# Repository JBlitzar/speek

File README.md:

# speek

A modular speaker system. Right now, it has a couple of boards:

- Speek Amp: This is the flagship amplifier. It's a hybrid 2.1 design using the TPA3116D2 chip. It's built to handle 4Ω speakers. It outputs lines for a mono subwoofer, two stereo woofers, and two stereo tweeters.
- Speek RX: This is a Bluetooth audio receiver. It runs off of a qfn esp32 D0WD v3 and has a built-in headphone amp, or a normal line out for chaining.
- Speek PSU: This is a supporting PSU board. It has a USB-C PD trigger (for quick tests) and a barrel jack port for proper power (needed to power real flagship drivers). It can be used as a stable power source for pretty much anything. Note that the barrel jack supplies 24V while PD gives 20V. 

On modularity:

- Each board is self-contained and can be used on its own. However, they can also all be used together. 

I made this project to get into audio systems! I've visited some hi-fi listening rooms, and I thought it was really cool. But I think the speaker industry is way overpriced. People commonly pay several thousand dollars for nice speaker systems! I wanted to build one myself for a few hundred. It might not be as high-fidelity, but it'll be my own, which is pretty cool. And you or I probably wouldn't be able to hear the difference. 

**Right now, enclosure design is out of scope. This repo holds just the boards, and the boards are complete**

## \[Please Read\] Where do I find everything? AKA checklist

What's with the monorepo?

A monorepo just means everything lives in one repo instead of splitting each board into its own. All the files are here: each board gets its own top-level folder (`speek-amp`, `speek-rx`, `speek-psu`), with docs in `docs` and the overall BOM at `BOM.csv`. I went with a monorepo because even though there are multiple boards, it's really one project overall, so it made sense to keep them together.

Checklist:

- [x] A good README
- [x] Source files for your project
    - This includes hardware design, firmware, 3D assemblies, etc
- [x] Production files (if applicable)
    - You'll find gerbers, fabrication BOMs, and PnP files at the following locations:
      - Speek Amp: [speek-amp/PCB/speek_amp/production_real](speek-amp/PCB/speek_amp/production_real)
      - Speek RX: [speek-rx/PCB/speek_rx/production_real](speek-rx/PCB/speek_rx/production_real)
      - Speek PSU: [speek-psu/PCB/speek_psu/production_real](speek-psu/PCB/speek_psu/production_real)
- \[N/A\] JOURNAL.md if journalling on Git
- [x] BOM.csv complete with functioning links (where applicable)
- [x] A short description of what your project is
- [x] A couple sentences on why you made the project
- [x] PICTURES OF YOUR PROJECT
- [x] A screenshot of your PCB, if you have one
- [x] A screenshot of your schematic, if you have one
- [x] A wiring diagram, if you're doing any wiring that isn't on a PCB
- [x] A BOM in table format at the end of the README
- [x] A STEP file of your assembly: [speek_assembly.step](docs/speek_assembly.step)

## How to use?

Mostly it's plug-and-play after assembling everything. The exception is Speek RX, which requires firmware to be flashed. See [speek-rx/README.md](speek-rx/README.md) for more info, but in short, all you should need to do is

```bash
cd speek-rx
cd firmware
pio run -t upload
```

For wiring your speaker drivers, the silkscreen should coach you through that. 

## Wiring Diagram

## Gallery

### Speek Amp

### Speek RX

### Speek PSU

## Schematics

### Speek Amp

[View on KiCanvas](https://kicanvas.org/?repo=https%3A%2F%2Fgithub.com%2FJBlitzar%2Fspeek%2Ftree%2Fmain%2Fspeek-amp%2FPCB%2Fspeek_amp)

### Speek RX

[View on KiCanvas](https://kicanvas.org/?repo=https%3A%2F%2Fgithub.com%2FJBlitzar%2Fspeek%2Ftree%2Fmain%2Fspeek-rx%2FPCB%2Fspeek_rx)

### Speek PSU

[View on KiCanvas](https://kicanvas.org/?repo=https%3A%2F%2Fgithub.com%2FJBlitzar%2Fspeek%2Ftree%2Fmain%2Fspeek-psu%2FPCB%2Fspeek_psu)

## PCBs

### Speek Amp

[View on KiCanvas](https://kicanvas.org/?repo=https%3A%2F%2Fgithub.com%2FJBlitzar%2Fspeek%2Ftree%2Fmain%2Fspeek-amp%2FPCB%2Fspeek_amp)

| F.Cu | B.Cu |
| --- | --- |
|  |  |

### Speek RX

[View on KiCanvas](https://kicanvas.org/?repo=https%3A%2F%2Fgithub.com%2FJBlitzar%2Fspeek%2Ftree%2Fmain%2Fspeek-rx%2FPCB%2Fspeek_rx)

| F.Cu | B.Cu |
| --- | --- |
|  |  |

### Speek PSU

[View on KiCanvas](https://kicanvas.org/?repo=https%3A%2F%2Fgithub.com%2FJBlitzar%2Fspeek%2Ftree%2Fmain%2Fspeek-psu%2FPCB%2Fspeek_psu)

| F.Cu | B.Cu |
| --- | --- |
|  |  |

## About cost

Speaker drivers are included in the BOM, but I'm not asking for them here. I will for sure pay for them out of pocket or figure it out. They are included in the BOM for record-keeping purposes. Basically they are the drivers that I sourced to base the amp design off of. 

For the rest, I have a significant amount of credits already lying around, and I've got a JLC $20 coupon. 

**TLDR:** I've heavily BOM-optimized and this is pretty much how much the PCBs are going to cost. Don't worry about the grant not covering everything, I'll pay the rest out of pocket

## Overall BOM

| Item | Link | Extended Cost | Notes |
| --- | --- | --- | --- |
| Notes | N/A | 0 | Will use some thick wire (already own) for all PSU bodge jobs. Speek RX must be 1mm thick PCB for antenna impedence matching! Subwoofer needs 1 cubic foot enclosure. |
| U.FL antenna | TBD | 0 | get this if the ceramic antenna doesnt work |
| 24v 6A PSU | https://www.amazon.com/Supply-Adapter-100-240V-Transformers-Security/dp/B0CGHSTDYM | 16 |  |
| XT60 male | https://www.lcsc.com/product-detail/C98733.html | 5 |  |
| XT60 female | https://www.lcsc.com/product-detail/C98734.html | 5 |  |
| JST VH connectors | https://www.amazon.com/pzsmocn-Extension-Accessories-Connector-Pre-Crimped/dp/B0DNPY3G91/ | 10 |  |
| preliminary subwoofer | https://www.parts-express.com/GRS-8SW-4-8-Poly-Cone-Subwoofer-4-Ohm-292-480?quantity=1 | 24 | [Note that I'm going to pay out of pocket for speaker drivers] Gamut runs $20 thru $50: see https://www.parts-express.com/speaker-components/hi-fi-woofers-subwoofers-midranges-tweeters/subwoofer-drivers/nominaldiameter/5-1--SLASH--4,6,6-1--SLASH--2,8?order=base_price:asc&base_price=0.00to78.49 ; pay $50 for fancier one https://www.parts-express.com/Dayton-Audio-SD215A-88-8-DVC-Subwoofer-295-484?quantity=1 |
| preliminary 2x woofers | https://www.parts-express.com/6-1-2-Poly-Cone-Woofer-4-Ohm-299-609?quantity=1 | 19.96 | [Note that I'm going to pay out of pocket for speaker drivers]  https://www.parts-express.com/reviewrating/4to5?order=custitem_pe_search_ranking:desc&keywords=woofers&base_price=0.00to40.81 . More expensive non-buyout option is https://www.parts-express.com/GRS-8PR-8-8-Poly-Cone-Rubber-Surround-Woofer-292-428?quantity=1 |
| preliminary 2x tweeters | https://www.parts-express.com/Dayton-Audio-ND20FA-6-3-4-Soft-Dome-Neodymium-Tweeter-275-030?quantity=1 | 21.96 | [Note that I'm going to pay out of pocket for speaker drivers]  https://www.parts-express.com/reviewrating/4to5?keywords=tweeter&base_price=0.00to24.71 ; There exists a $4 per listing |
| 47uF caps | https://www.lcsc.com/product-detail/C397097.html | 0.76 | Buying straight from LCSC to hand-solder instead of PCBAing |
| 22uF caps | https://www.lcsc.com/product-detail/C216548.html | 0.53 | Buying straight from LCSC to hand-solder instead of PCBAing |
| 10uF caps | https://www.lcsc.com/product-detail/C192100.html | 0.74 | Buying straight from LCSC to hand-solder instead of PCBAing |
| 6.8uF film caps | https://www.lcsc.com/product-detail/C21390242.html | 1.87 | Buying straight from LCSC to hand-solder instead of PCBAing |
| 150uH inductor | https://www.lcsc.com/product-detail/C3011544.html | 1.02 | Buying straight from LCSC to hand-solder instead of PCBAing |
| 2x 4700uF cap | https://www.lcsc.com/product-detail/C5115284.html | 3.86 | Buying straight from LCSC to hand-solder instead of PCBAing |
| 1x tht diode | https://www.lcsc.com/product-detail/C522740.html | 0.72 | Buying straight from LCSC to hand-solder instead of PCBAing |
| 10x screw terminal | https://www.lcsc.com/product-detail/C695629.html | 0.84 | Buying straight from LCSC to hand-solder instead of PCBAing |
| LCSC shipping | N/A | 18.37 |  |
| Speek Amp PCB | N/A | 8.6 |  |
| Speek Amp PCBA | N/A | 45.18 |  |
| Speek RX PCB | N/A | 4 |  |
| Speek RX PCBA | N/A | 73.48 |  |
| Speek PSU PCB | N/A | 2 |  |
| JLC Shipping | N/A | 29 |  |
| Total |  | 292.89 |  |
| Total (excluding speaker drivers) |  | 226.97 |  |
| PCB total |  | 190.97 |  |

## Fabrication BOMs

> LCSC part numbers missing? Don't worry, it's a DNP component that I'll hand solder myself. It's in the table above.

### Speek Amp

| Designator | Footprint | Quantity | Value | LCSC Part # |
| --- | --- | --- | --- | --- |
| C1, C16, C43, C54, C55, C8 | C0402 | 6 | 100nF | C307331 |
| C10, C17, C26, C27, C28, C29, C56, C57, C68, C69, C7 | C0402 | 11 | 1nF | C1523 |
| C11, C12, C13, C14, C48, C49, C50, C51 | C0402 | 8 | 220nF | C16772 |
| C15, C52, C53, C9 | CAP-SMD_BD8.0-L8.3-W8.3-FD | 4 | 220uF | C178534 |
| C18, C19, C20, C21, C22, C23 | C0603 | 6 | 10nF | C57112 |
| C2 | C0603 | 1 | 100nF | C14663 |
| C3, C36 | CAP-TH_L29.5-W12.7-P27.00-D0.8 | 2 | 6.8uF film | C21390242 |
| C30, C31, C32, C33, C41, C42, C45, C6 | C0402 | 8 | 1uF | C52923 |
| C34, C35, C39, C40 | CP_Radial_D6.3mm_P2.50mm | 4 | 10uF |  |
| C37, C4 | CP_Radial_D6.3mm_P2.50mm | 2 | 47uF |  |
| C38, C5 | CP_Radial_D6.3mm_P2.50mm | 2 | 22uF |  |
| C44, C46, C47, C60, C61, C70 | C0805 | 6 | 680nF | C107133 |
| IN_1 | AUDIO-SMD_PJ-320D-1 | 1 | PJ-320D | C431535 |
| R1, R13, R18, R19, R6, R7, R8, R9 | R0402 | 8 | 3.3 | C137986 |
| R10 | R0805 | 1 | 5.6k | C4382 |
| R11 | R0603 | 1 | 3.2k | C861375 |
| R12 | R0603 | 1 | 47k | C25819 |
| R14, R15, R2, R5 | R0402 | 4 | 100k | C25741 |
| R20, R3, R4 | R0402 | 3 | 10k | C25744 |
| R21 | R0603 | 1 | 75k | C23242 |
| U1, U10 | HTSSOP-32_L11.0-W6.1-P0.65-LS8.1-BL | 2 | TPA3116D2DAD_C2865736 | C2865736 |
| U11 | CONN-TH_DB301V-3.5-2P-GN | 1 | R_Tweeter | C695629 |
| U12 | CONN-TH_DB301V-3.5-2P-GN | 1 | R_Woofer | C695629 |
| U13, U14, U2, U3, U5, U6 | IND-SMD_L7.2-W6.6_GPSR07X0 | 6 | 10uH | C5189958 |
| U15 | CONN-TH_DB301V-3.5-2P-GN | 1 | L_Tweeter | C695629 |
| U16 | CONN-TH_DB301V-3.5-2P-GN | 1 | L_Woofer | C695629 |
| U17 | CONN-TH_DB301V-3.5-2P-GN | 1 | L_Sub | C695629 |
| U18 | CONN-TH_DB301V-3.5-2P-GN | 1 | J1 | C695629 |
| U4 | CONN-TH_XT60 | 1 | XT60 | C98733 |
| U7, U8 | IND-TH_L23.0-W12.0-P8.00-D0.8 | 2 | PDMTAT068125-151MLU | C3011544 |
| U9 | CAP-TH_BD18.0-P7.50-D0.8-FD | 1 | 50PX4700MEFC18X40 | C5115284 |

### Speek RX

| Designator | Footprint | Quantity | Value | LCSC Part # |
| --- | --- | --- | --- | --- |
| AE1 | ANT-SMD_L3.2-W1.6 | 1 | 2450AT18A100E | C89334 |
| BOOT1, EN1 | SW-SMD_4P-L5.1-W5.1-P3.70-LS6.5-TL_H1.5 | 2 | TS-1187A-B-A-B | C318884 |
| C16, C23, C24, C27, C28, C40 | C0402 | 6 | 10uF | C15525 |
| C18, C19, C20, C22, C25, C26, C29, C39 | C0402 | 8 | 0.1uF | C1525 |
| C21 | C0402 | 1 | CL05A475KP5NRNC | C23733 |
| C30, C31, C36, C37 | C0402 | 4 | CL05A225MQ5NSNC | C12530 |
| C32, C33, C34, C35 | C0402 | 4 | 1uF | C52923 |
| C38 | C0402 | 1 | 1pF | C309455 |
| CN1, CN2 | AUDIO-SMD_PJ-320D-1 | 2 | PJ-320D | C431535 |
| D2 | SOD-323_L1.7-W1.3-LS2.5-BI-1 | 1 | PESD3V3L1BA | C2827682 |
| JP1 | RF-SMD_FRF05002-JSS103M | 1 | U.FL-R-SMT-1 | C88374 |
| L4 | IND-SMD_L1.0-W0.5-2 | 1 | 3.9nH | C98062 |
| L5 | L0402 | 1 | 2.7nH | C27123 |
| Q1, Q2 | SOT-23-3_L2.9-W1.5-P1.90-LS2.6-BR | 2 | SS8050 | C2150 |
| R10, R11, R7 | R0402 | 3 | 10k | C25744 |
| R4 | R0402 | 1 | RC0402FR-071KL | C11702 |
| R5 | R0402 | 1 | 47k | C25792 |
| R6 | R0402 | 1 | 22k | C25768 |
| R8 | R0402 | 1 | 0402WGF0000TCE | C17168 |
| R9 | R0603 | 1 | 0R | C21189 |
| U19 | QFN-48_L7.0-W7.0-P0.50-BL-EP5.1 | 1 | ESP32-PICO-V3-02 | C908392 |
| U3 | QFN-24_L4.0-W4.0-P0.50-TL-EP2.6 | 1 | CP2102N-A02-GQFN24R | C969151 |
| U4 | SOT-223-4_L6.5-W3.5-P2.30-LS7.0-BR | 1 | AMS1117-3.3 | C6186 |
| U5 | TSSOP-20_L6.5-W4.4-P0.65-LS6.4-BL | 1 | PCM5102APW | C1520792 |
| U6 | WQFN-16_L3.0-W3.0-P0.50-TL-EP1.6 | 1 | TPA6132A2RTER | C69901 |
| USB1 | USB-C-SMD_TYPE-C-16PIN-2MD-073 | 1 | TYPE-C 16PIN 2MD | C2765186 |

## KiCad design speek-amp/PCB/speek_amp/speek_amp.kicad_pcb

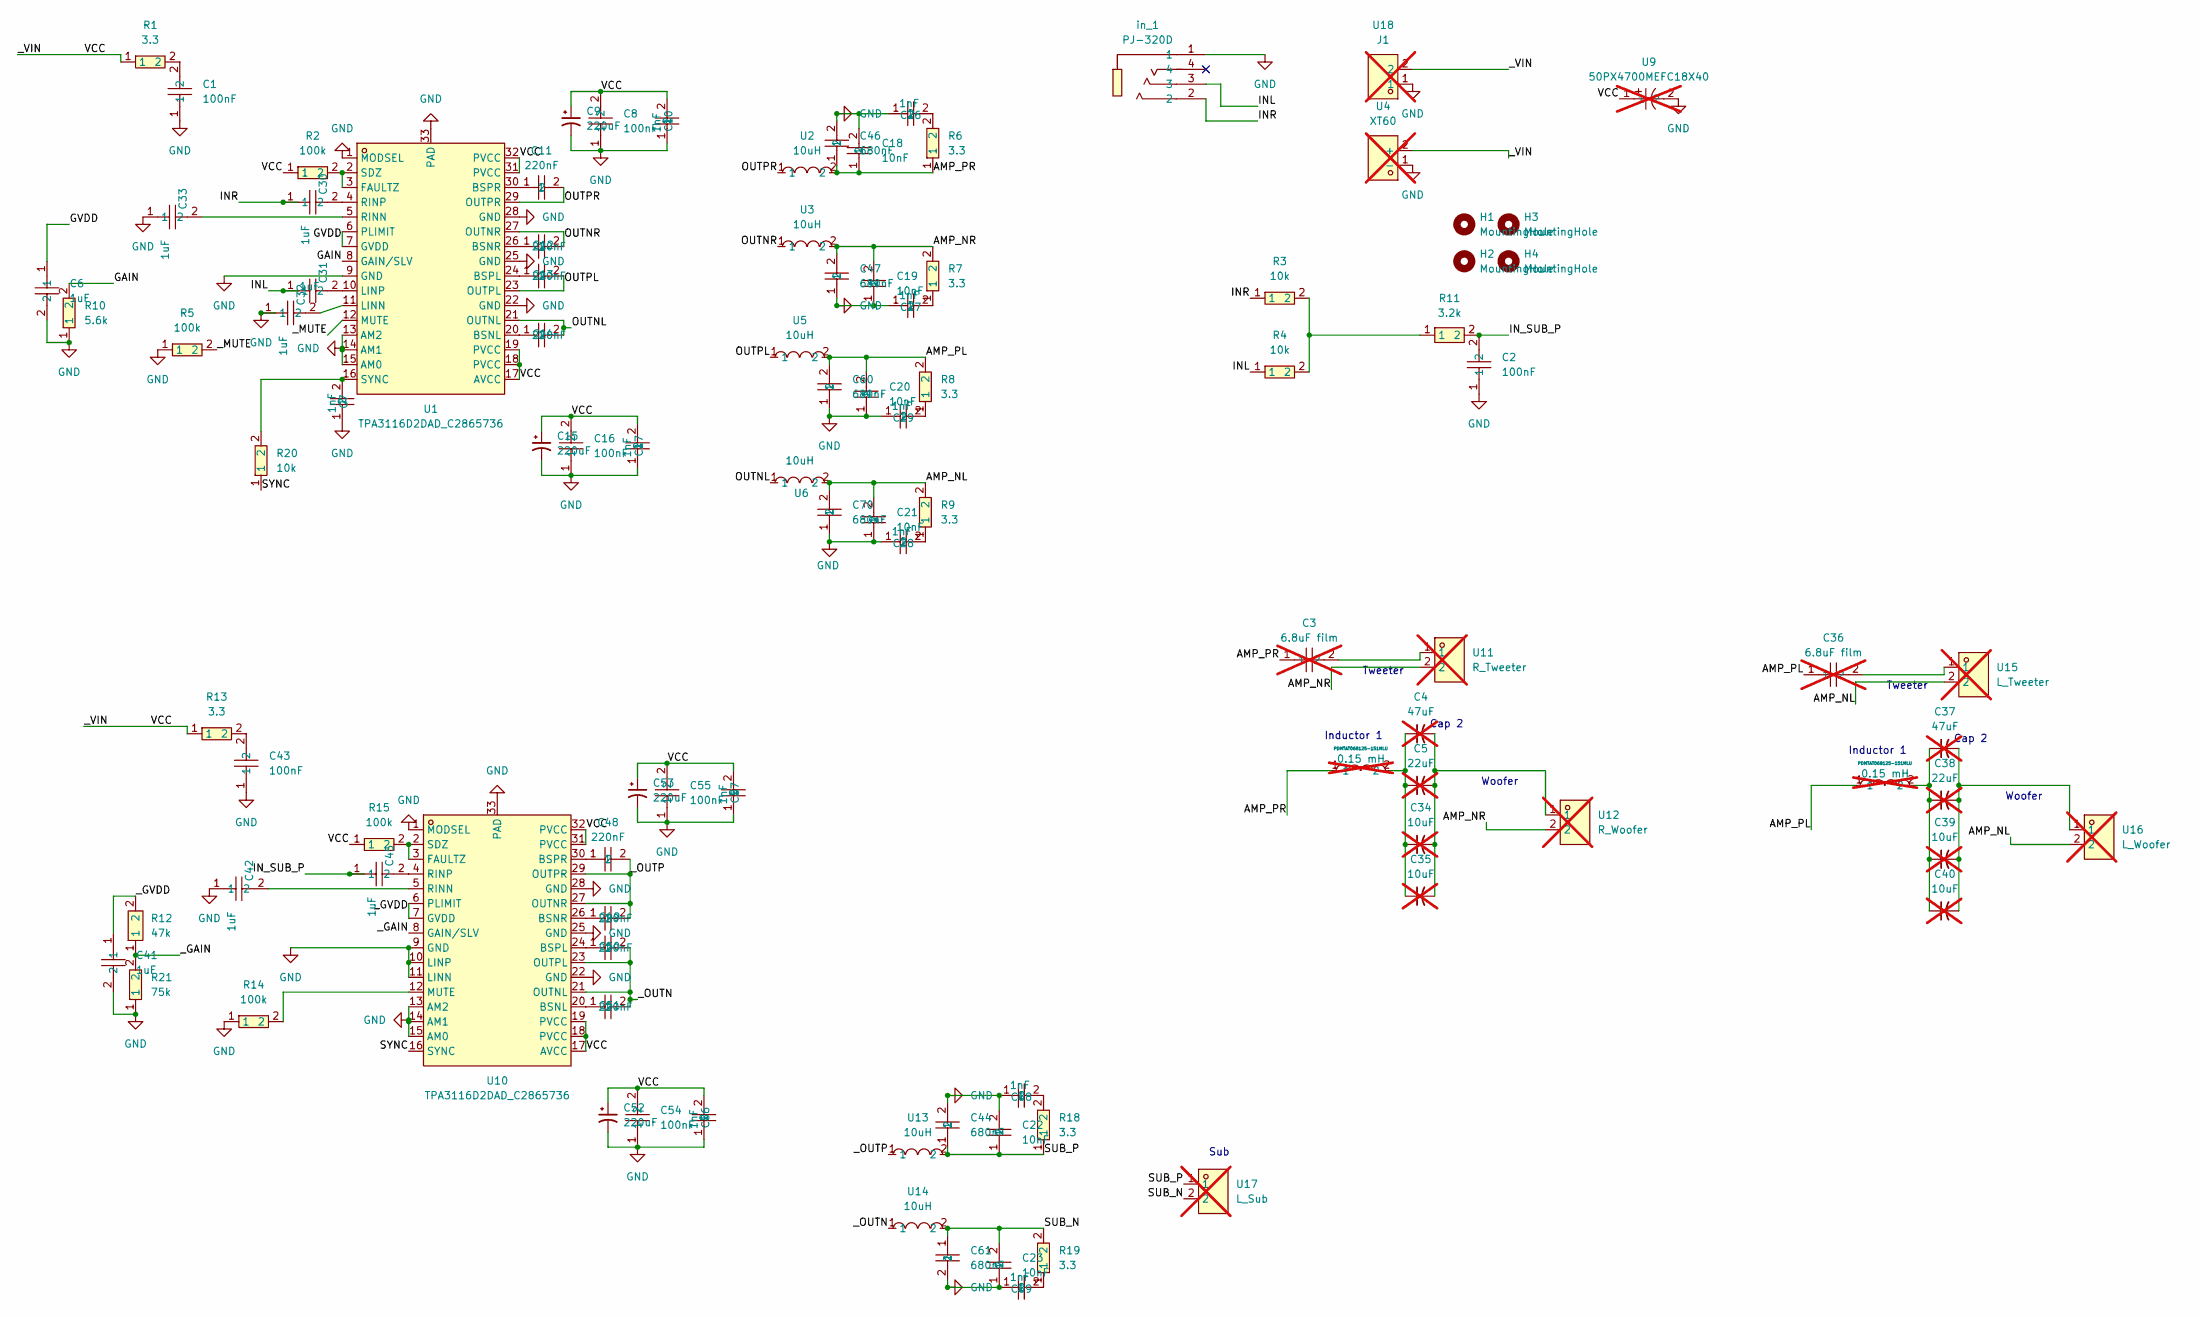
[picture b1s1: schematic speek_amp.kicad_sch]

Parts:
C1, C8, C16, C43, C54, C55: 100nF; C0402; MPN CL05B104KB54PNC; LCSC Part C307331
C2: 100nF; C0603; MPN CC0603KRX7R9BB104; LCSC Part C14663
C3, C36: 6.8uF film; CAP-TH_L29.5-W12.7-P27.00-D0.8; MPN W312G685JS8SA1C0EC; LCSC Part C21390242; not fitted
C4, C37: 47uF; CP_Radial_D6.3mm_P2.50mm; not fitted
C5, C38: 22uF; CP_Radial_D6.3mm_P2.50mm; not fitted
C6, C30, C31, C32, C33, C41, C42, C45: 1uF; C0402; MPN CL05A105KA5NQNC; LCSC Part C52923
C7, C10, C17, C26, C27, C28, C29, C56, C57, C68, C69: 1nF; C0402; MPN 0402B102K500NT; LCSC Part C1523
C9, C15, C52, C53: 220uF; CAP-SMD_BD8.0-L8.3-W8.3-FD
C11, C12, C13, C14, C48, C49, C50, C51: 220nF; C0402; MPN CL05B224KO5NNNC; LCSC Part C16772
C18, C19, C20, C21, C22, C23: 10nF; C0603; MPN 0603B103K500NT; LCSC Part C57112
C34, C35, C39, C40: 10uF; CP_Radial_D6.3mm_P2.50mm; not fitted
C44, C46, C47, C60, C61, C70: 680nF; C0805; MPN CC0805KKX7R9BB684; LCSC Part C107133
H1, H2, H3, H4: MountingHole; MountingHole_3.2mm_M3
R1, R6, R7, R8, R9, R13, R18, R19: 3.3; R0402; MPN RC0402FR-073R3L; LCSC Part C137986
R2, R5, R14, R15: 100k; R0402; MPN 0402WGF1003TCE; LCSC Part C25741
R3, R4, R20: 10k; R0402; MPN 0402WGF1002TCE; LCSC Part C25744
R10: 5.6k; R0805; MPN 0805W8F5601T5E; LCSC Part C4382
R11: 3.2k; R0603; MPN RT0603BRD073K2L; LCSC Part C861375
R12: 47k; R0603; MPN 0603WAF4702T5E; LCSC Part C25819
R21: 75k; R0603; MPN 0603WAF7502T5E; LCSC Part C23242
U1, U10: TPA3116D2DAD_C2865736; HTSSOP-32_L11.0-W6.1-P0.65-LS8.1-BL; MPN TPA3116D2DAD; LCSC Part C2865736
U2, U3, U5, U6, U13, U14: 10uH; IND-SMD_L7.2-W6.6_GPSR07X0; MPN CYA0630-10UH; LCSC Part C5189958
U4: XT60; CONN-TH_XT60; MPN XT60-M.; LCSC Part C98733; not fitted
U7, U8: PDMTAT068125-151MLU; IND-TH_L23.0-W12.0-P8.00-D0.8; MPN PDMTAT068125-151MLU; LCSC Part C3011544; not fitted
U9: 50PX4700MEFC18X40; CAP-TH_BD18.0-P7.50-D0.8-FD; MPN 50PX4700MEFC18X40; LCSC Part C5115284; not fitted
U11: R_Tweeter; CONN-TH_DB301V-3.5-2P-GN; MPN DB301V-3.5-2P-GN-S; LCSC Part C695629; not fitted
U12: R_Woofer; CONN-TH_DB301V-3.5-2P-GN; MPN DB301V-3.5-2P-GN-S; LCSC Part C695629; not fitted
U15: L_Tweeter; CONN-TH_DB301V-3.5-2P-GN; MPN DB301V-3.5-2P-GN-S; LCSC Part C695629; not fitted
U16: L_Woofer; CONN-TH_DB301V-3.5-2P-GN; MPN DB301V-3.5-2P-GN-S; LCSC Part C695629; not fitted
U17: L_Sub; CONN-TH_DB301V-3.5-2P-GN; MPN DB301V-3.5-2P-GN-S; LCSC Part C695629; not fitted
U18: J1; CONN-TH_DB301V-3.5-2P-GN; MPN DB301V-3.5-2P-GN-S; LCSC Part C695629; not fitted
in_1: PJ-320D; AUDIO-SMD_PJ-320D-1; MPN PJ-320D; LCSC Part C431535

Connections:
/AMP_NL: C21.2, C70.2, R9.2, U6.2, U15.2, U16.2
/AMP_NR: C19.2, C47.2, R7.2, U3.2, U11.2, U12.2
/AMP_PL: C20.2, C36.1, C60.2, R8.2, U5.2, U8.1
/AMP_PR: C3.1, C18.1, C46.1, R6.1, U2.2, U7.1
/GAIN: R10.2, U1.8 (GAIN/SLV)
/GVDD: C6.1, U1.6 (PLIMIT), U1.7 (GVDD)
/INL: C31.1, R4.1, in_1.3
/INR: C30.1, R3.1, in_1.2
/IN_SUB_P: C2.2, C45.1, R11.2
/OUTNL: C14.2, U1.21 (OUTNL), U6.1
/OUTNR: C12.2, U1.27 (OUTNR), U3.1
/OUTPL: C13.2, U1.23 (OUTPL), U5.1
/OUTPR: C11.2, U1.29 (OUTPR), U2.1
/SUB_N: C23.2, C61.1, R19.2, U14.2, U17.2
/SUB_P: C22.1, C44.1, R18.1, U13.2, U17.1
/SYNC: R20.1, U10.16 (SYNC)
/VCC: C8.2, C9.1, C10.2, C15.1, C16.2, C17.2, C52.1, C53.1, C54.2, C55.2, C56.2, C57.2, R1.1, R2.1, R13.1, R15.1, U1.17 (AVCC), U1.18 (PVCC), U1.19 (PVCC), U1.31 (PVCC), U1.32 (PVCC), U4.2 (+), U9.1, U10.17 (AVCC), U10.18 (PVCC), U10.19 (PVCC), U10.31 (PVCC), U10.32 (PVCC), U18.2
/_GAIN: R12.1, R21.2, U10.8 (GAIN/SLV)
/_GVDD: C41.1, R12.2, U10.6 (PLIMIT), U10.7 (GVDD)
/_MUTE: R5.2, U1.12 (MUTE)
/_OUTN: C50.2, C51.2, U10.21 (OUTNL), U10.23 (OUTPL), U14.1
/_OUTP: C48.2, C49.2, U10.27 (OUTNR), U10.29 (OUTPR), U13.1
GND: C1.1, C2.1, C6.2, C7.1, C8.1, C9.2, C10.1, C15.2, C16.1, C17.1, C18.2, C19.1, C20.1, C21.1, C22.2, C23.1, C26.1, C27.1, C28.1, C29.1, C32.1, C33.1, C41.2, C42.1, C43.1, C44.2, C46.2, C47.1, C52.2, C53.2, C54.1, C55.1, C56.1, C57.1, C60.1, C61.2, C68.1, C69.1, C70.1, R5.1, R10.1, R14.1, R21.1, U1.1 (MODSEL), U1.9 (GND), U1.13 (AM2), U1.14 (AM1), U1.15 (AM0), U1.22 (GND), U1.25 (GND), U1.28 (GND), U1.33 (PAD), U4.1 (-), U9.2, U10.1 (MODSEL), U10.9 (GND), U10.10 (LINP), U10.11 (LINN), U10.13 (AM2), U10.14 (AM1), U10.15 (AM0), U10.22 (GND), U10.25 (GND), U10.28 (GND), U10.33 (PAD), U18.1, in_1.1
unnamed: C1.2, R1.2
unnamed: C3.2, U11.1
unnamed: C26.2, R6.2
unnamed: C27.2, R7.1
unnamed: C28.2, R9.1
unnamed: C29.2, R8.1
unnamed: C4.1, C5.1, C34.1, C35.1, U7.2
unnamed: C4.2, C5.2, C34.2, C35.2, U12.1
unnamed: C36.2, U15.1
unnamed: C37.1, C38.1, C39.1, C40.1, U8.2
unnamed: C37.2, C38.2, C39.2, C40.2, U16.1
unnamed: C43.2, R13.2
unnamed: C68.2, R18.2
unnamed: C69.2, R19.1
unnamed: R3.2, R4.2, R11.1
unnamed: C14.1, U1.20 (BSNL)
unnamed: C12.1, U1.26 (BSNR)
unnamed: C13.1, U1.24 (BSPL)
unnamed: C11.1, U1.30 (BSPR)
unnamed: R2.2, U1.2 (SDZ), U1.3 (FAULTZ)
unnamed: C32.2, U1.11 (LINN)
unnamed: C31.2, U1.10 (LINP)
unnamed: C33.2, U1.5 (RINN)
unnamed: C30.2, U1.4 (RINP)
unnamed: C7.2, R20.2, U1.16 (SYNC)
unnamed: C51.1, U10.20 (BSNL)
unnamed: C49.1, U10.26 (BSNR)
unnamed: C50.1, U10.24 (BSPL)
unnamed: C48.1, U10.30 (BSPR)
unnamed: R15.2, U10.2 (SDZ), U10.3 (FAULTZ)
unnamed: R14.2, U10.12 (MUTE)
unnamed: C42.2, U10.5 (RINN)
unnamed: C45.2, U10.4 (RINP)

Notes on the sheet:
Inductor 1
Woofer
Tweeter
Cap 2
Sub

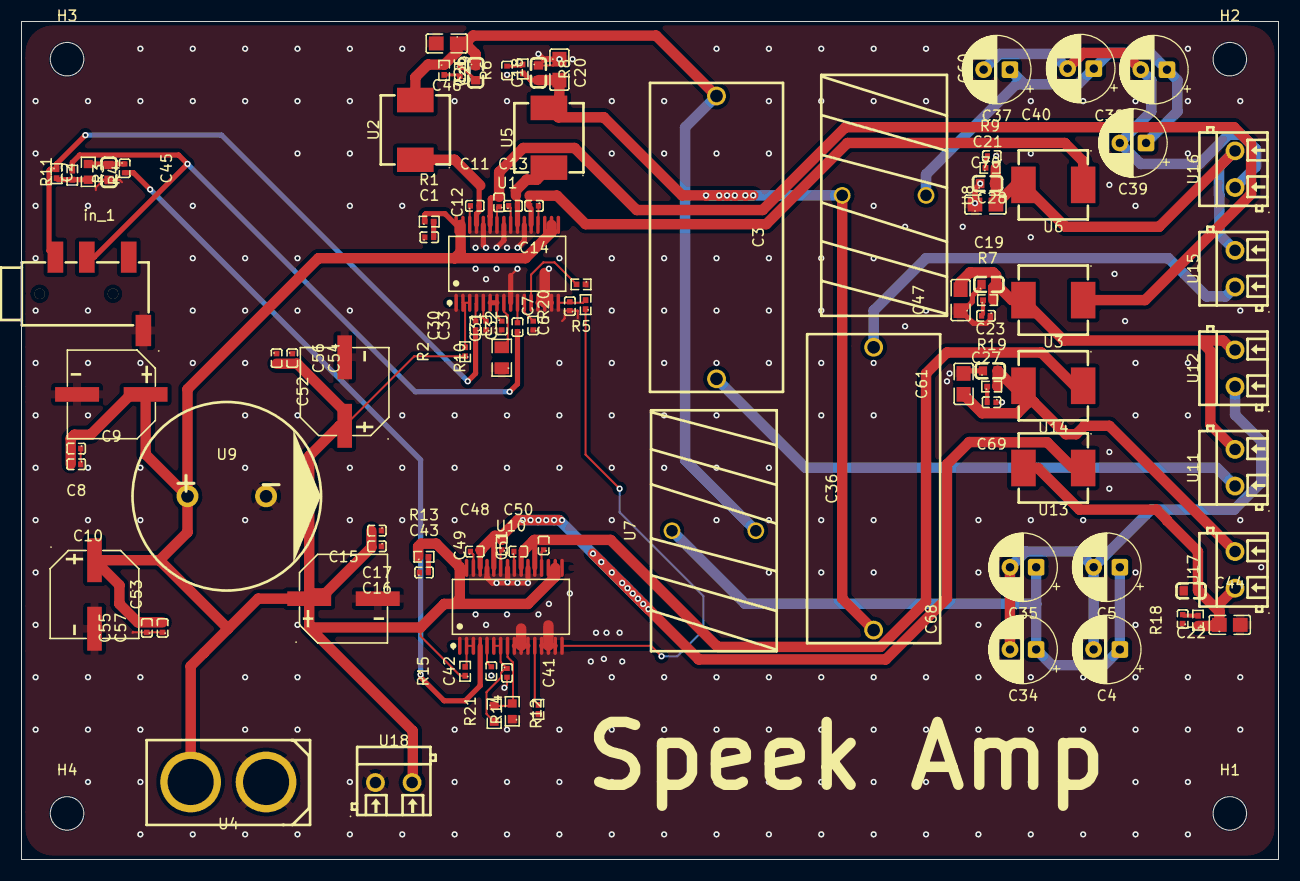
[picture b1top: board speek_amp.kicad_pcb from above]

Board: 2 copper layers, 120.0 x 80.0 mm, 102 parts (0 on the bottom side), 56 nets.

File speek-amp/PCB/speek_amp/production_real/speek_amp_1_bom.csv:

Designator,Footprint,Quantity,Value,LCSC Part #
"C1, C16, C43, C54, C55, C8",C0402,6,100nF,C307331
"C10, C17, C26, C27, C28, C29, C56, C57, C68, C69, C7",C0402,11,1nF,C1523
"C11, C12, C13, C14, C48, C49, C50, C51",C0402,8,220nF,C16772
"C15, C52, C53, C9",CAP-SMD_BD8.0-L8.3-W8.3-FD,4,220uF,C178534
"C18, C19, C20, C21, C22, C23",C0603,6,10nF,C57112
C2,C0603,1,100nF,C14663
"C3, C36",CAP-TH_L29.5-W12.7-P27.00-D0.8,2,6.8uF film,C21390242
"C30, C31, C32, C33, C41, C42, C45, C6",C0402,8,1uF,C52923
"C34, C35, C39, C40",CP_Radial_D6.3mm_P2.50mm,4,10uF,
"C37, C4",CP_Radial_D6.3mm_P2.50mm,2,47uF,
"C38, C5",CP_Radial_D6.3mm_P2.50mm,2,22uF,
"C44, C46, C47, C60, C61, C70",C0805,6,680nF,C107133
IN_1,AUDIO-SMD_PJ-320D-1,1,PJ-320D,C431535
"R1, R13, R18, R19, R6, R7, R8, R9",R0402,8,3.3,C137986
R10,R0805,1,5.6k,C4382
R11,R0603,1,3.2k,C861375
R12,R0603,1,47k,C25819
"R14, R15, R2, R5",R0402,4,100k,C25741
"R20, R3, R4",R0402,3,10k,C25744
R21,R0603,1,75k,C23242
"U1, U10",HTSSOP-32_L11.0-W6.1-P0.65-LS8.1-BL,2,TPA3116D2DAD_C2865736,C2865736
U11,CONN-TH_DB301V-3.5-2P-GN,1,R_Tweeter,C695629
U12,CONN-TH_DB301V-3.5-2P-GN,1,R_Woofer,C695629
"U13, U14, U2, U3, U5, U6",IND-SMD_L7.2-W6.6_GPSR07X0,6,10uH,C5189958
U15,CONN-TH_DB301V-3.5-2P-GN,1,L_Tweeter,C695629
U16,CONN-TH_DB301V-3.5-2P-GN,1,L_Woofer,C695629
U17,CONN-TH_DB301V-3.5-2P-GN,1,L_Sub,C695629
U18,CONN-TH_DB301V-3.5-2P-GN,1,J1,C695629
U4,CONN-TH_XT60,1,XT60,C98733
"U7, U8",IND-TH_L23.0-W12.0-P8.00-D0.8,2,PDMTAT068125-151MLU,C3011544
U9,CAP-TH_BD18.0-P7.50-D0.8-FD,1,50PX4700MEFC18X40,C5115284

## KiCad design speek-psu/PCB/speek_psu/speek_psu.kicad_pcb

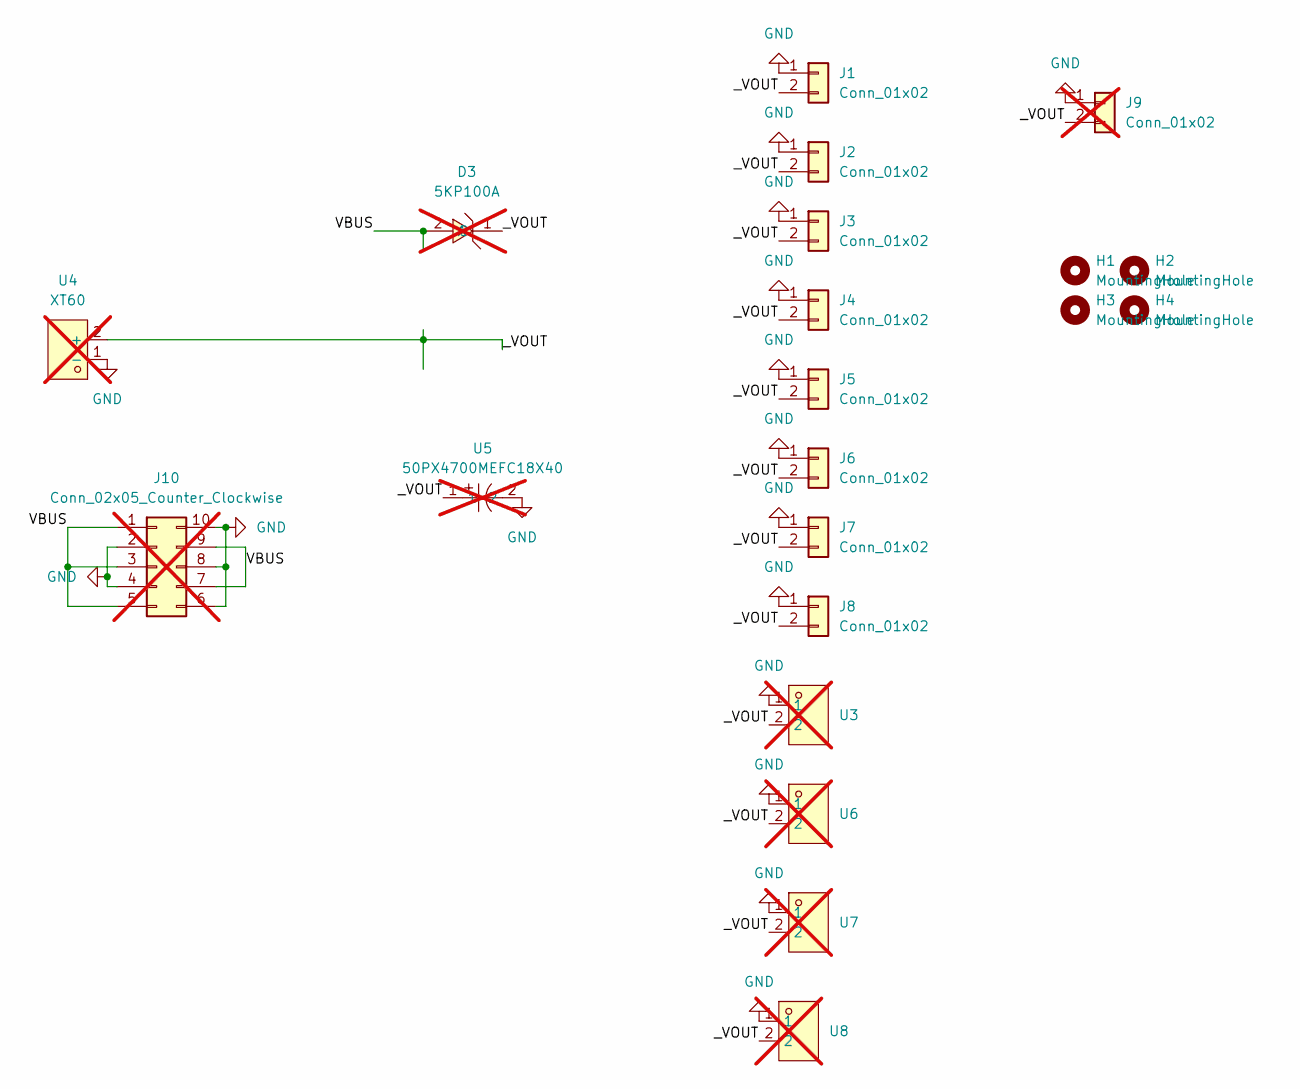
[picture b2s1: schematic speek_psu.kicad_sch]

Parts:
D3: 5KP100A; DIO-TH_BD8.8-L8.8-P12.8-D1.6-RD; MPN 5KP100A/B; LCSC Part C522740; not fitted
H1, H2, H3, H4: MountingHole; MountingHole_3.2mm_M3
J1, J2, J3, J4, J5, J6, J7, J8: Conn_01x02; JST_VH_B2P-VH-B_1x02_P3.96mm_Vertical
J9: Conn_01x02; PinHeader_1x02_P2.54mm_Horizontal; not fitted
J10: Conn_02x05_Counter_Clockwise; PinHeader_2x05_P2.54mm_Horizontal; not fitted
U3, U6, U7, U8: CONN-TH_DB301V-3.5-2P-GN; MPN DB301V-3.5-2P-GN-S; LCSC Part C695629; not fitted
U4: XT60; CONN-TH_XT60; MPN XT60-M.; LCSC Part C98733; not fitted
U5: 50PX4700MEFC18X40; CAP-TH_BD18.0-P7.50-D0.8-FD; MPN 50PX4700MEFC18X40; LCSC Part C5115284; not fitted

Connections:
/VBUS: D3.2 (A), J10.1, J10.3, J10.5, J10.7, J10.9
/_VOUT: D3.1 (C), J1.2, J2.2, J3.2, J4.2, J5.2, J6.2, J7.2, J8.2, J9.2, U3.2, U4.2 (+), U5.1, U6.2, U7.2, U8.2
GND: J1.1, J2.1, J3.1, J4.1, J5.1, J6.1, J7.1, J8.1, J9.1, J10.2, J10.4, J10.6, J10.8, J10.10, U3.1, U4.1 (-), U5.2, U6.1, U7.1, U8.1

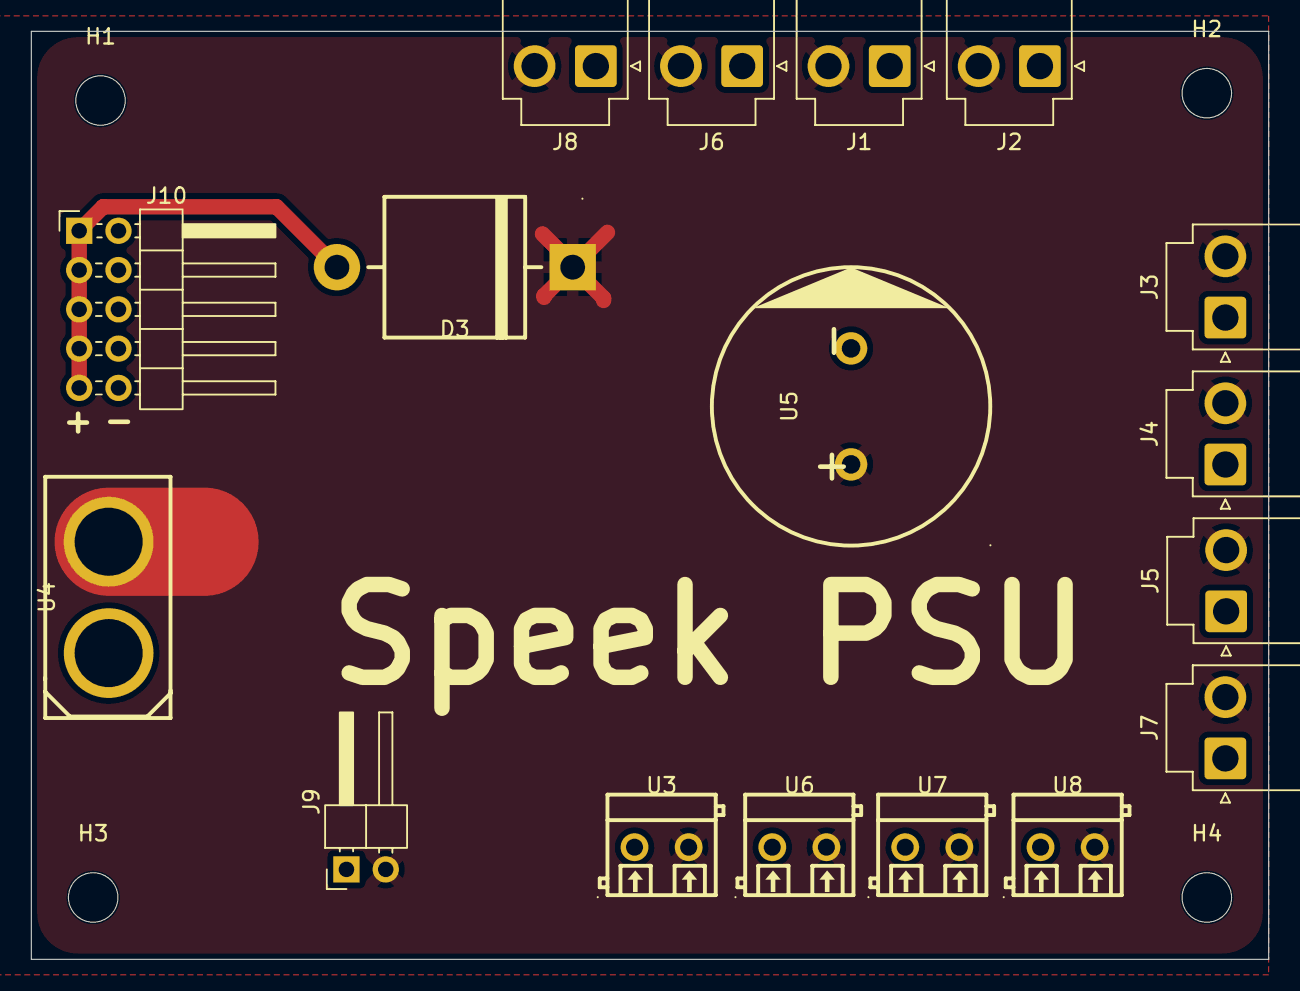
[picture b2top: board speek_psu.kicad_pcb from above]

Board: 2 copper layers, 80.0 x 60.0 mm, 21 parts (0 on the bottom side), 3 nets.

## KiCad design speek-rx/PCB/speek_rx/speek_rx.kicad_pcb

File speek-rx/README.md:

# speek-rx
Bluetooth to 3.5mm adapter. 

## How to use

Plug the USB-C port in to your computer.

Flash:
```bash
cd firmware
pio run -t upload
```

Now you can run the usb-c port off of a power brick or whatever

Speaker should show up in bluetooth as "speek-rx." Enjoy!

Line out and headphone jack are labeled in silkscreen

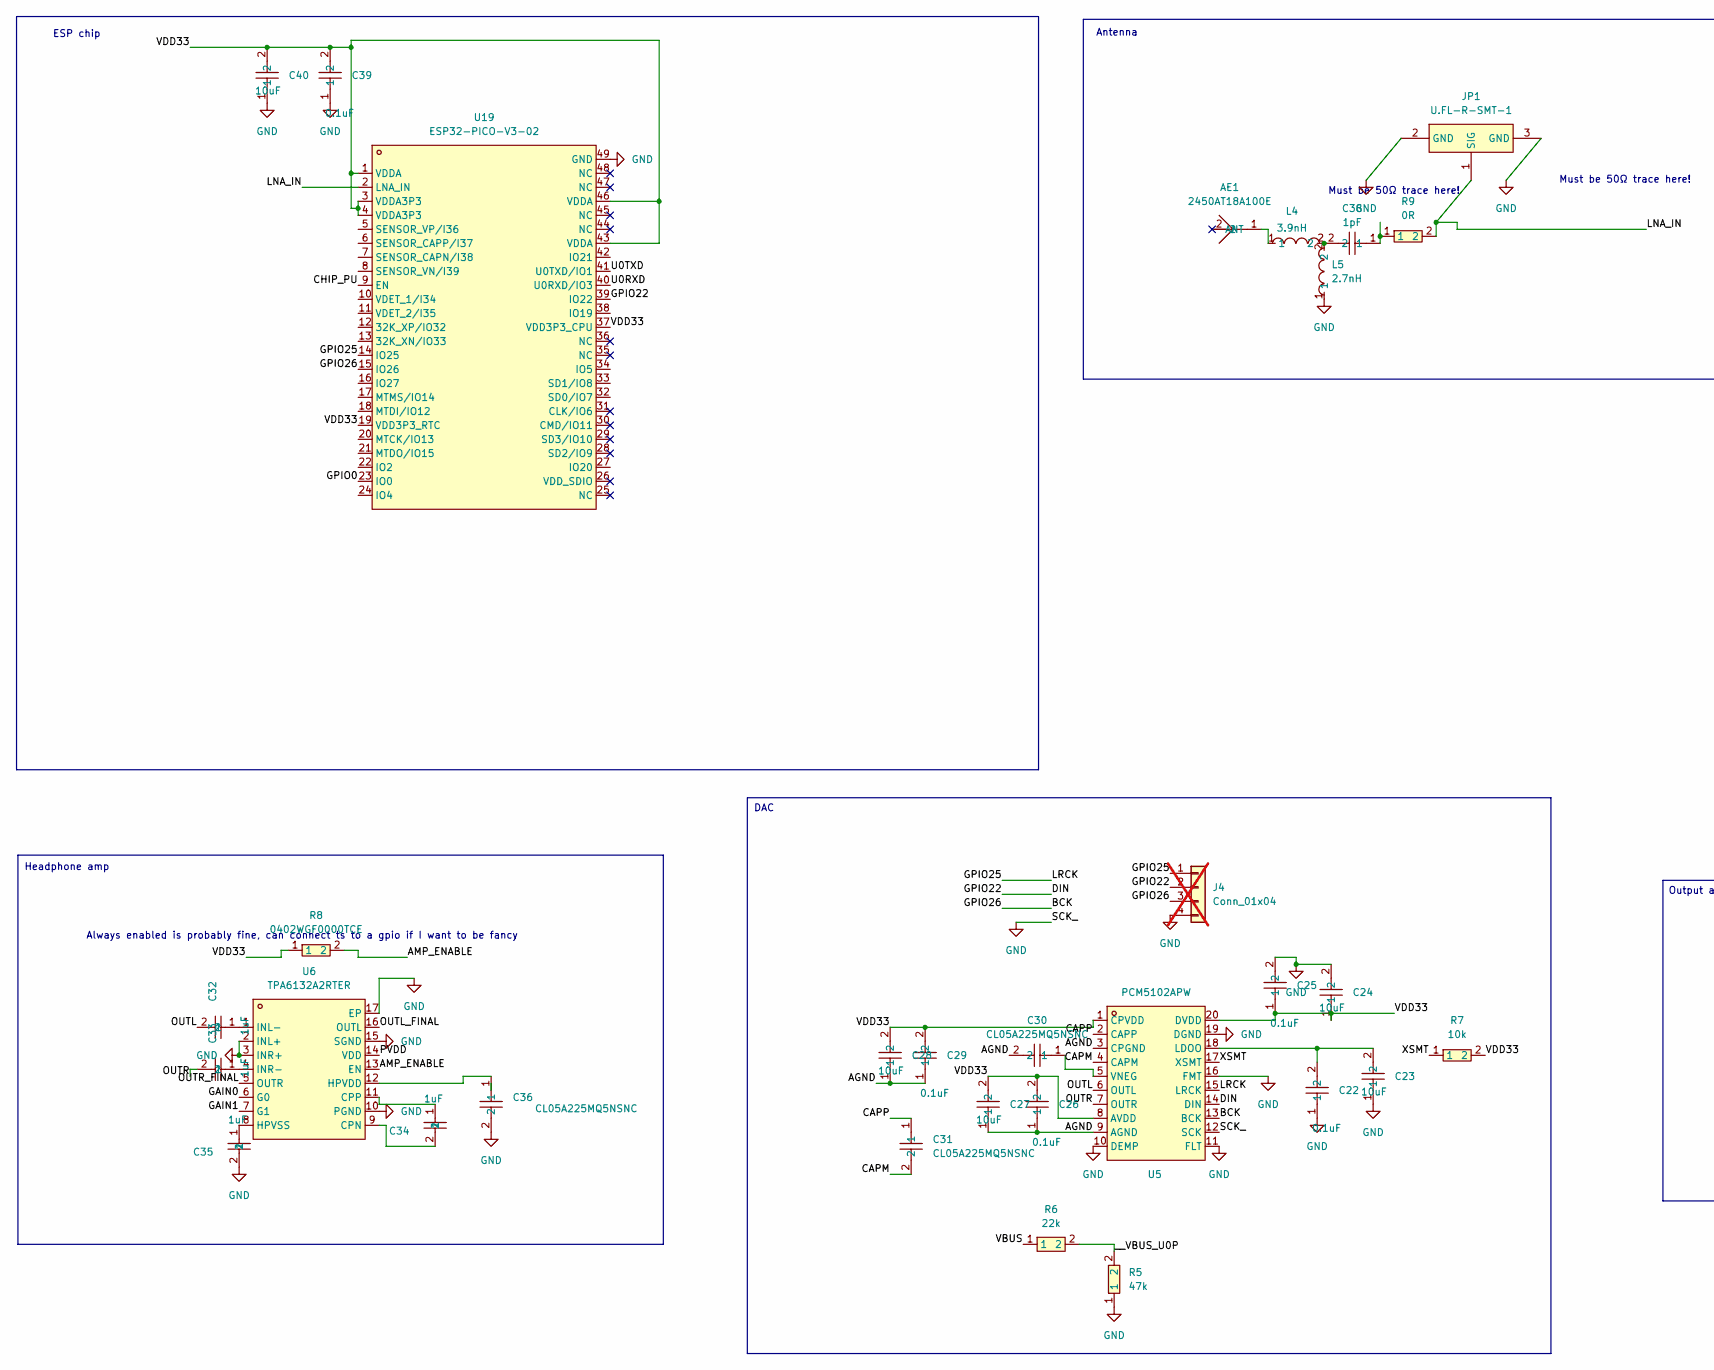
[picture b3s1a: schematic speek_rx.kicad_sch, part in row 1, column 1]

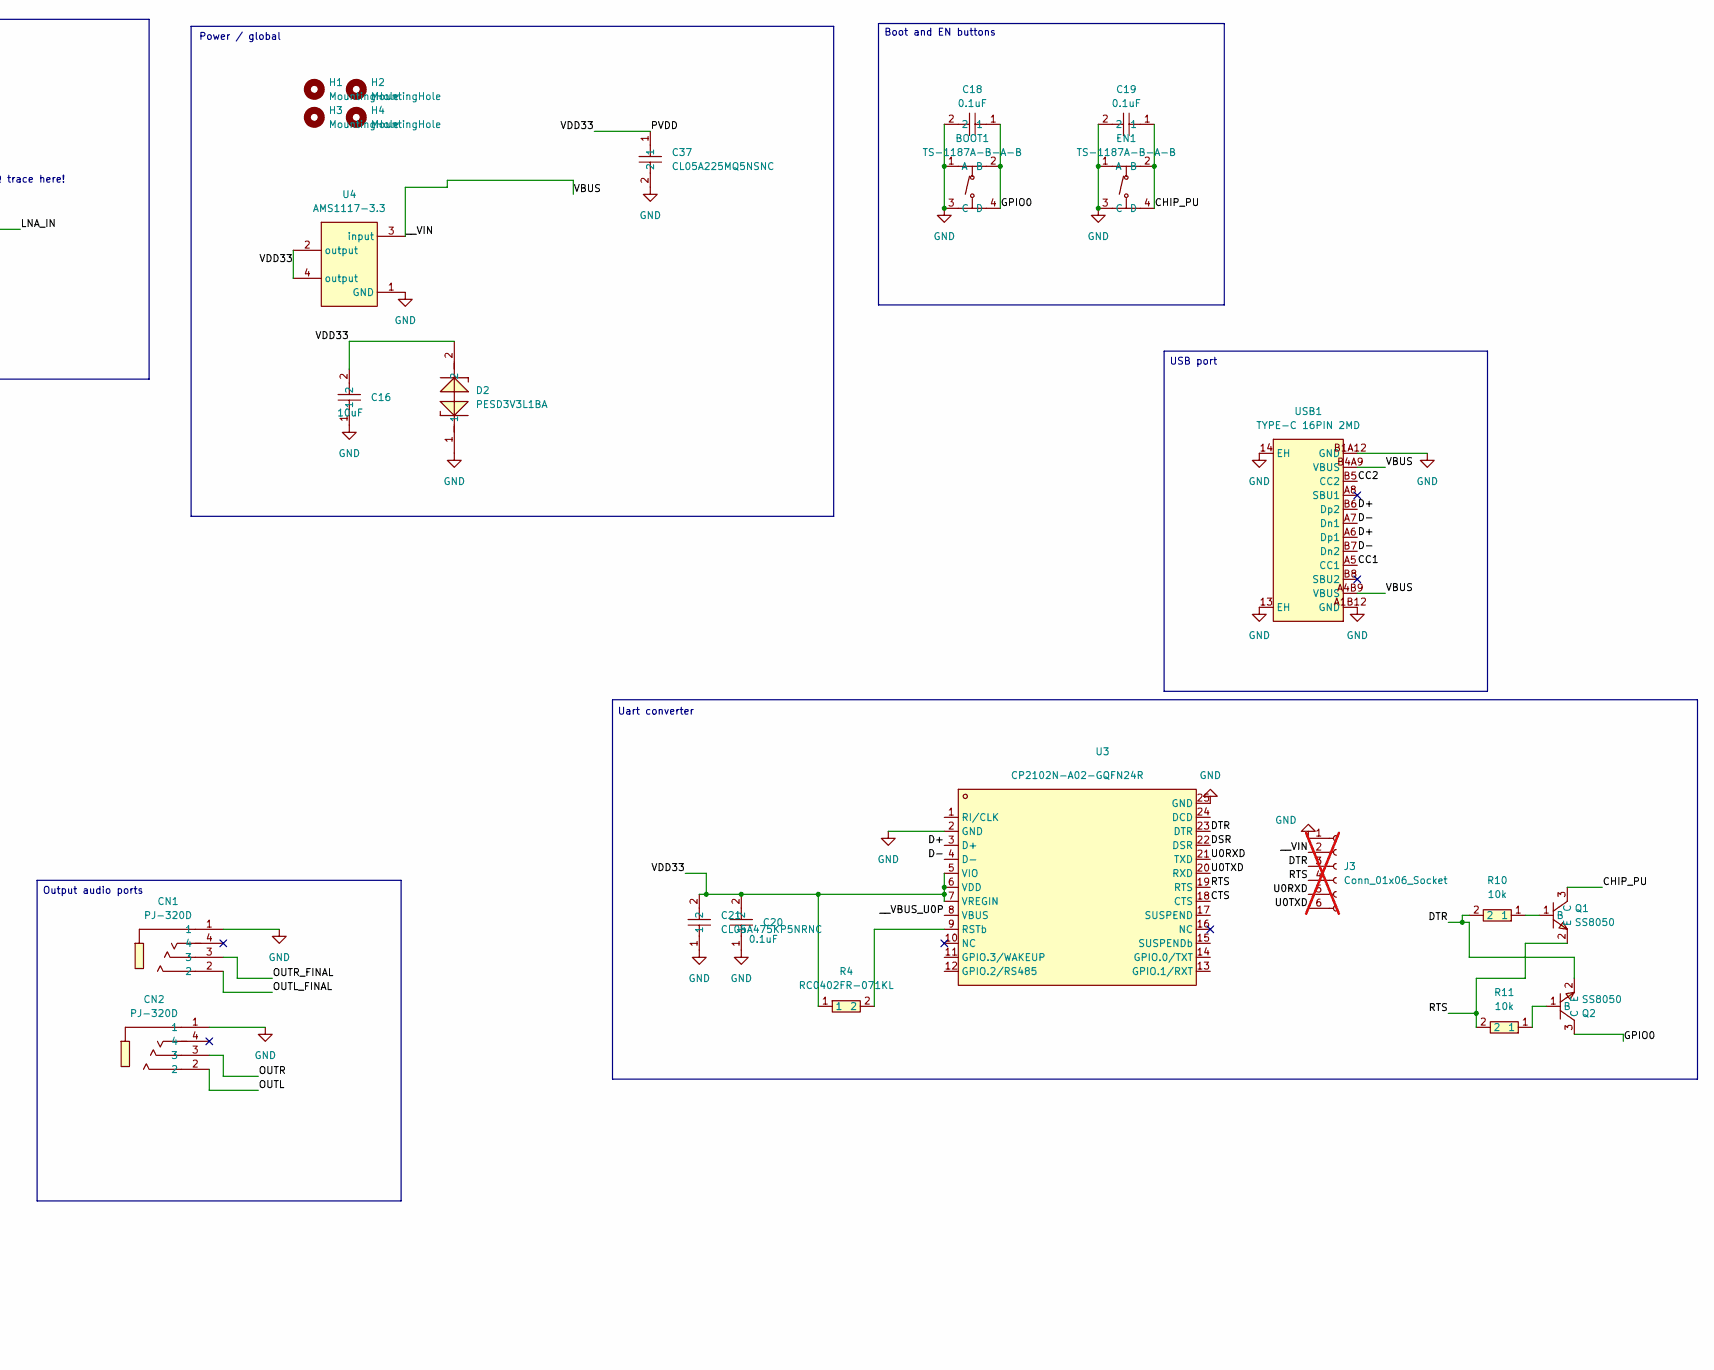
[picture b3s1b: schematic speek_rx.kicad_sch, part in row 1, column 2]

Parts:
AE1: 2450AT18A100E; ANT-SMD_L3.2-W1.6; MPN 2450AT18A100E; LCSC Part C89334
BOOT1: TS-1187A-B-A-B; SW-SMD_4P-L5.1-W5.1-P3.70-LS6.5-TL_H1.5; MPN TS-1187A-B-A-B; LCSC Part C318884
C16, C23, C24, C27, C28, C40: 10uF; C0402; MPN CL05A106MQ5NUNC; LCSC Part C15525
C18, C19, C20, C22, C25, C26, C29, C39: 0.1uF; C0402; MPN CL05B104KO5NNNC; LCSC Part C1525
C21: CL05A475KP5NRNC; C0402; MPN CL05A475KP5NRNC; LCSC Part C23733
C30, C31, C36, C37: CL05A225MQ5NSNC; C0402; MPN CL05A225MQ5NSNC; LCSC Part C12530
C32, C33, C34, C35: 1uF; C0402; MPN CL05A105KA5NQNC; LCSC Part C52923
C38: 1pF; C0402; MPN CC0402BRNPO9BN1R0; LCSC Part C309455
CN1, CN2: PJ-320D; AUDIO-SMD_PJ-320D-1; MPN PJ-320D; LCSC Part C431535
D2: PESD3V3L1BA; SOD-323_L1.7-W1.3-LS2.5-BI-1; MPN PESD3V3L1BA; LCSC Part C2827682
EN1: TS-1187A-B-A-B; SW-SMD_4P-L5.1-W5.1-P3.70-LS6.5-TL_H1.5; MPN TS-1187A-B-A-B; LCSC Part C318884
H1, H2, H3, H4: MountingHole; MountingHole_3.2mm_M3
J3: Conn_01x06_Socket; PinHeader_1x06_P2.54mm_Horizontal; not fitted
J4: Conn_01x04; PinHeader_1x04_P2.54mm_Horizontal; not fitted
JP1: U.FL-R-SMT-1; RF-SMD_FRF05002-JSS103M; MPN U.FL-R-SMT-1(80); LCSC Part C88374
L4: 3.9nH; IND-SMD_L1.0-W0.5-2; MPN LQW15AN3N9B00D; LCSC Part C98062
L5: 2.7nH; L0402; MPN SDCL1005C2N7STDF; LCSC Part C27123
Q1, Q2: SS8050; SOT-23-3_L2.9-W1.5-P1.90-LS2.6-BR; MPN SS8050(RANGE:200-350); LCSC Part C2150
R4: RC0402FR-071KL; R0402; MPN RC0402FR-071KL; LCSC Part C11702
R5: 47k; R0402; MPN 0402WGF4702TCE; LCSC Part C25792
R6: 22k; R0402; MPN 0402WGF2202TCE; LCSC Part C25768
R7, R10, R11: 10k; R0402; MPN 0402WGF1002TCE; LCSC Part C25744
R8: 0402WGF0000TCE; R0402; MPN 0402WGF0000TCE; LCSC Part C17168
R9: 0R; R0603; MPN 0603WAF0000T5E; LCSC Part C21189
U3: CP2102N-A02-GQFN24R; QFN-24_L4.0-W4.0-P0.50-TL-EP2.6; MPN CP2102N-A02-GQFN24R; LCSC Part C969151
U4: AMS1117-3.3; SOT-223-4_L6.5-W3.5-P2.30-LS7.0-BR; MPN AMS1117-3.3; LCSC Part C6186
U5: PCM5102APW; TSSOP-20_L6.5-W4.4-P0.65-LS6.4-BL; MPN PCM5102APW; LCSC Part C1520792
U6: TPA6132A2RTER; WQFN-16_L3.0-W3.0-P0.50-TL-EP1.6; MPN TPA6132A2RTER; LCSC Part C69901
U19: ESP32-PICO-V3-02; QFN-48_L7.0-W7.0-P0.50-BL-EP5.1; MPN ESP32-PICO-V3-02; LCSC Part C908392
USB1: TYPE-C 16PIN 2MD; USB-C-SMD_TYPE-C-16PIN-2MD-073; MPN TYPE-C 16PIN 2MD(073); LCSC Part C2765186

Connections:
/AGND: C26.1, C27.1, C28.1, C29.1, C30.2, U5.3 (CPGND), U5.9 (AGND)
/AMP_ENABLE: R8.2, U6.13 (EN)
/BCK: J4.3, U5.13 (BCK), U19.15 (IO26)
/CAPM: C31.2, U5.4 (CAPM)
/CAPP: C31.1, U5.2 (CAPP)
/CC1: USB1.A5 (CC1)
/CC2: USB1.B5 (CC2)
/CHIP_PU: C19.1, EN1.2 (B), EN1.4 (D), Q1.3 (C), U19.9 (EN)
/CTS: U3.18 (CTS)
/D+: U3.3 (D+), USB1.A6 (Dp1), USB1.B6 (Dp2)
/D-: U3.4 (D-), USB1.A7 (Dn1), USB1.B7 (Dn2)
/DIN: J4.2, U5.14 (DIN), U19.39 (IO22)
/DSR: U3.22 (DSR)
/DTR: J3.3, Q2.2 (E), R10.2, U3.23 (DTR)
/GAIN0: U6.6 (G0)
/GAIN1: U6.7 (G1)
/GPIO0: BOOT1.2 (B), BOOT1.4 (D), C18.1, Q2.3 (C), U19.23 (IO0)
/GPIO25: J4.1, U5.15 (LRCK), U19.14 (IO25)
/LNA_IN: JP1.1 (SIG), R9.2, U19.2 (LNA_IN)
/OUTL: C32.2, CN2.2, U5.6 (OUTL)
/OUTL_FINAL: CN1.2, U6.16 (OUTL)
/OUTR: C33.2, CN2.3, U5.7 (OUTR)
/OUTR_FINAL: CN1.3, U6.5 (OUTR)
/PVDD: C16.2, C20.2, C21.2, C24.1, C25.1, C26.2, C27.2, C28.2, C29.2, C37.1, C39.2, C40.2, D2.2, R4.1, R7.2, R8.1, U3.5 (VIO), U3.6 (VDD), U3.7 (VREGIN), U4.2 (output), U4.4 (output), U5.1 (CPVDD), U5.8 (AVDD), U5.20 (DVDD), U6.14 (VDD), U19.1 (VDDA), U19.3 (VDDA3P3), U19.4 (VDDA3P3), U19.19 (VDD3P3_RTC), U19.37 (VDD3P3_CPU), U19.43 (VDDA), U19.46 (VDDA)
/RTS: J3.4, Q1.2 (E), R11.2, U3.19 (RTS)
/U0RXD: J3.5, U3.21 (TXD), U19.40 (U0RXD/IO3)
/U0TXD: J3.6, U3.20 (RXD), U19.41 (U0TXD/IO1)
/VBUS: J3.2, R6.1, U4.3 (input), USB1.A4B9 (VBUS), USB1.B4A9 (VBUS)
/XSMT: R7.1, U5.17 (XSMT)
/__VBUS_U0P: R5.2, R6.2, U3.8 (VBUS)
GND: BOOT1.1 (A), BOOT1.3 (C), C16.1, C18.2, C19.2, C20.1, C21.1, C22.1, C23.1, C24.2, C25.2, C35.2, C36.2, C37.2, C39.1, C40.1, CN1.1, CN2.1, D2.1, EN1.1 (A), EN1.3 (C), J3.1, J4.4, JP1.2 (GND), JP1.3 (GND), L5.1, R5.1, U3.2 (GND), U3.25 (GND), U4.1 (GND), U5.10 (DEMP), U5.11 (FLT), U5.12 (SCK), U5.16 (FMT), U5.19 (DGND), U6.2 (INL+), U6.3 (INR+), U6.10 (PGND), U6.15 (SGND), U6.17 (EP), U19.49 (GND), USB1.13 (EH), USB1.14 (EH), USB1.A1B12 (GND), USB1.B1A12 (GND)
unnamed: AE1.1 (ANT_1), L4.1
unnamed: C38.1, R9.1
unnamed: C38.2, L4.2, L5.2
unnamed: Q1.1 (B), R10.1
unnamed: Q2.1 (B), R11.1
unnamed: R4.2, U3.9 (RSTb)
unnamed: C22.2, C23.2, U5.18 (LDOO)
unnamed: C30.1, U5.5 (VNEG)
unnamed: C34.2, U6.9 (CPN)
unnamed: C34.1, U6.11 (CPP)
unnamed: C36.1, U6.12 (HPVDD)
unnamed: C35.1, U6.8 (HPVSS)
unnamed: C32.1, U6.1 (INL-)
unnamed: C33.1, U6.4 (INR-)

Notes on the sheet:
DAC
USB port
Headphone amp
Must be 50Ω trace here!
Antenna
ESP chip
Always enabled is probably fine, can connect ts to a gpio if I want to be fancy
Output audio ports
Power / global
Boot and EN buttons
Uart converter
